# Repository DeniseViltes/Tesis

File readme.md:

# Plataforma experimental de ecualización activa de celdas de litio

Trabajo Profesional de Ingeniería Electrónica  
Facultad de Ingeniería – Universidad de Buenos Aires (FIUBA)  
Año 2026

**Integrantes**
- Sebastián Ezequiel García
- Denise Oriana Viltes

**Tutora:** Dra. Cecilia G. Galarza  
**Cotutor:** Ing. Juan Zuloaga

---

## Descripción

Este proyecto presenta el diseño, simulación e implementación de una plataforma
experimental para evaluar estrategias de ecualización activa en baterías de litio.

La plataforma permite:
- reconfigurar dinámicamente el conexionado de celdas mediante una matriz de switches
<!-- Esto es un comentario --> - estimar SoC (State of Charge)
<!-- Esto es un comentario -->- ensayar algoritmos de balanceo activo
- validar resultados mediante simulación y prototipo físico

El objetivo es contar con una plataforma para comparar
distintas arquitecturas de balanceo y analizar su eficiencia energética.

---

## Estructura del repositorio

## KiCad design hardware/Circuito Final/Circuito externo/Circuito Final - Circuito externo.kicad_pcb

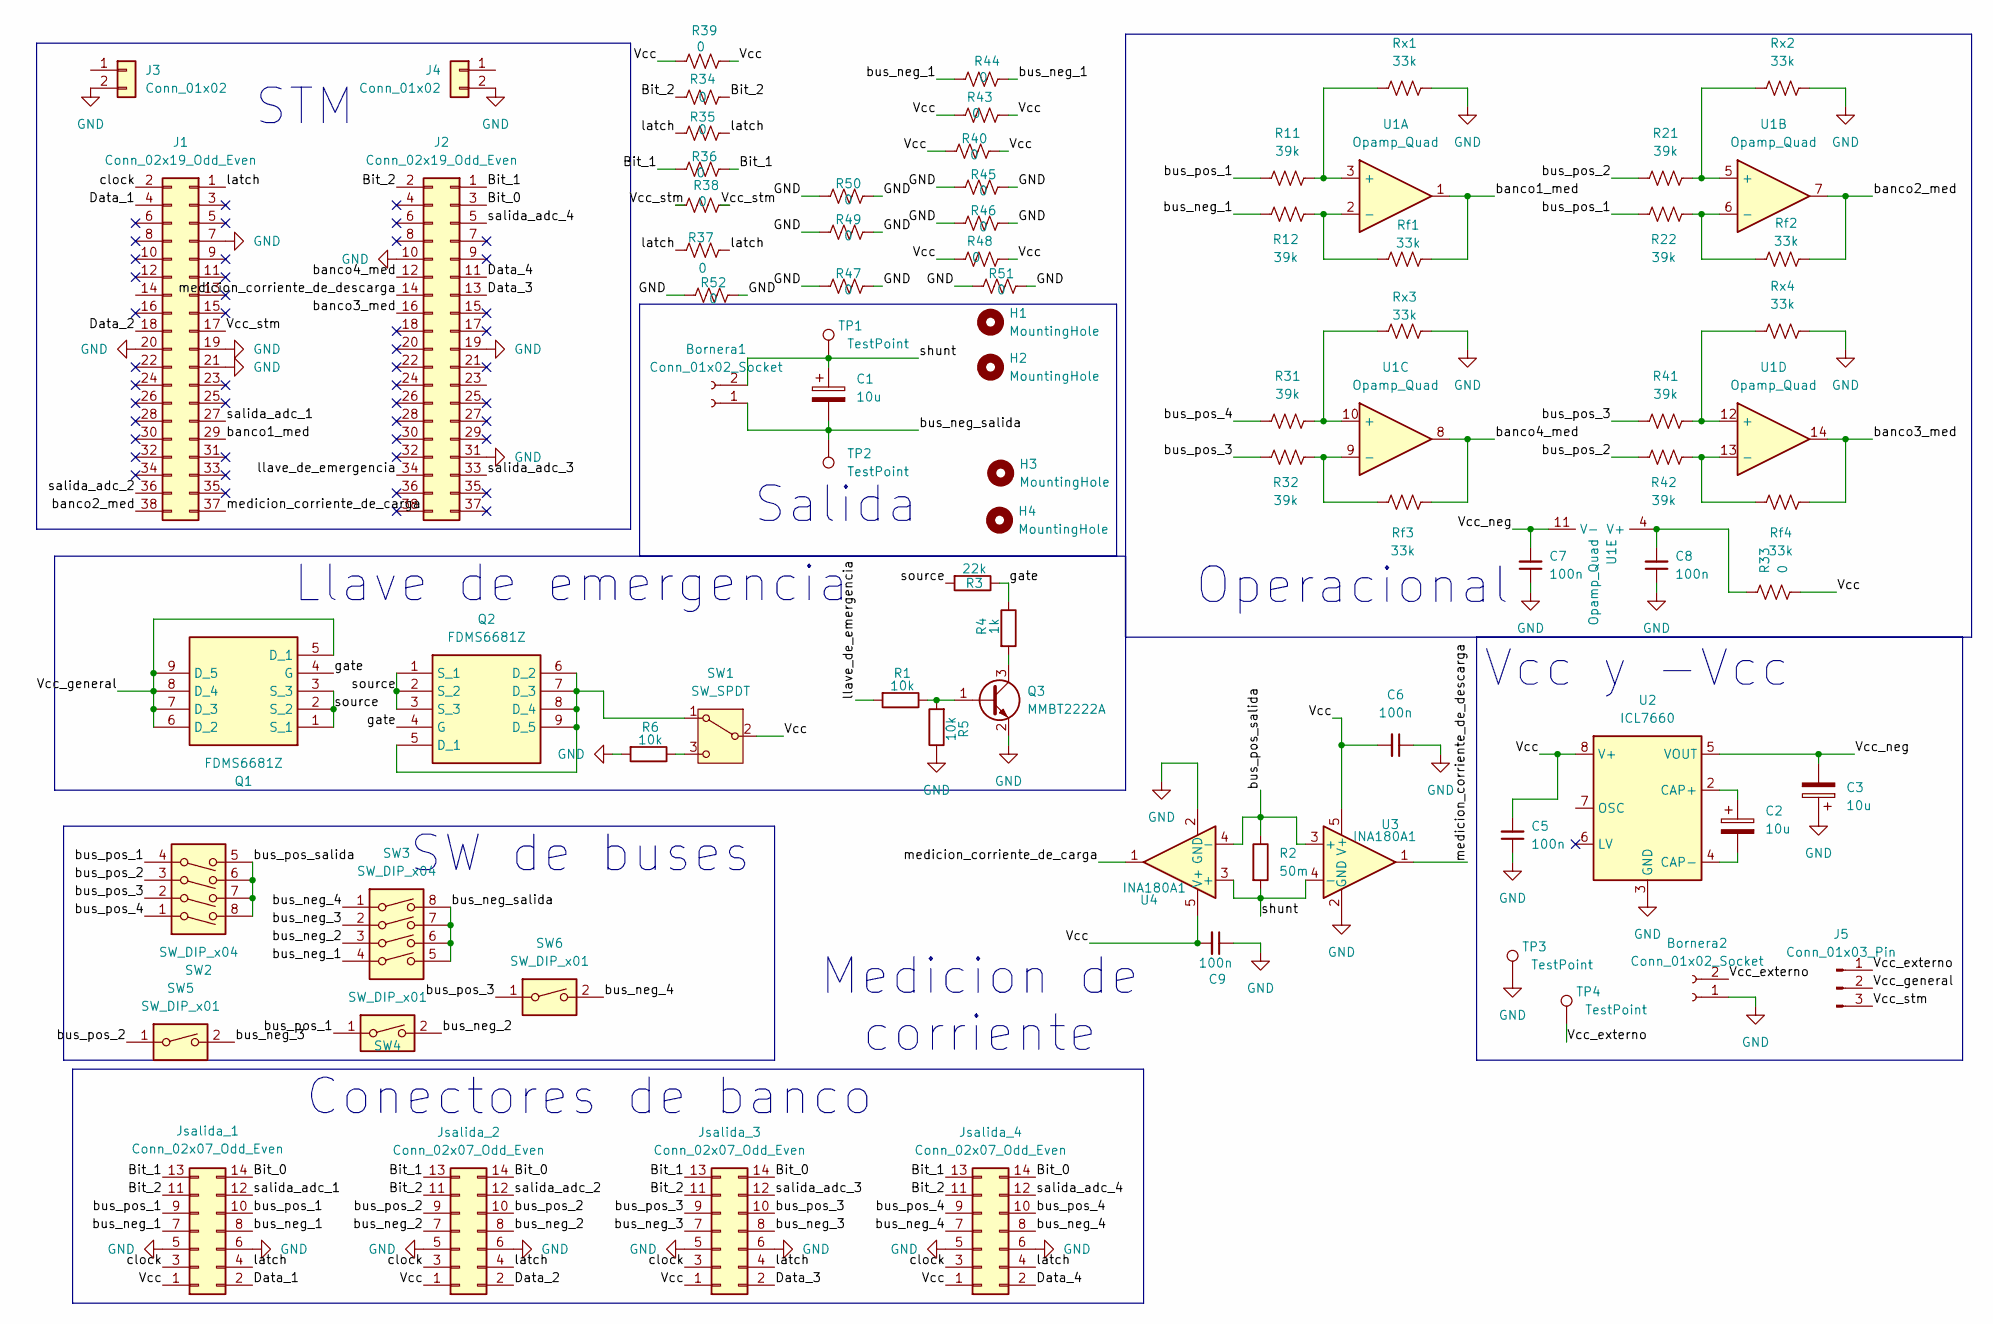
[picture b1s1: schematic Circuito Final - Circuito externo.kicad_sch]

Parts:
Bornera1, Bornera2: Conn_01x02_Socket; TerminalBlock_bornier-2_P5.08mm
C1, C2, C3: 10u; C_1206_3216Metric_Pad1.33x1.80mm_HandSolder
C5, C6, C7, C8, C9: 100n; C_1206_3216Metric_Pad1.33x1.80mm_HandSolder
H1, H2, H3, H4: MountingHole; MountingHole_3.5mm
J1, J2: Conn_02x19_Odd_Even; PinSocket_2x19_P2.54mm_Vertical
J3, J4: Conn_01x02; PinSocket_1x02_P2.54mm_Vertical
J5: Conn_01x03_Pin; PinHeader_1x03_P2.54mm_Vertical
Jsalida_1, Jsalida_2, Jsalida_3, Jsalida_4: Conn_02x07_Odd_Even; IDC-Header_2x07_P2.54mm_Horizontal
Q1, Q2: FDMS6681Z; Mouser Part Number 512-FDMS6681Z
Q3: MMBT2222A; SOT-23
R1, R5, R6: 10k; R_1206_3216Metric_Pad1.30x1.75mm_HandSolder
R2: 50m; R_2512_6332Metric_Pad1.40x3.35mm_HandSolder
R3: 22k; R_1206_3216Metric_Pad1.30x1.75mm_HandSolder
R4: 1k; R_1206_3216Metric_Pad1.30x1.75mm_HandSolder
R11, R12, R21, R22, R31, R32, R41, R42: 39k; R_1206_3216Metric_Pad1.30x1.75mm_HandSolder
R33, R34, R35, R36, R37, R38, R39, R40, R43, R44, R45, R46, R47, R48, R49, R50, R51, R52: 0; R_1206_3216Metric_Pad1.30x1.75mm_HandSolder
Rf1, Rf2, Rf3, Rf4: 33k; R_1206_3216Metric_Pad1.30x1.75mm_HandSolder
Rx1, Rx2, Rx3, Rx4: 33k; R_1206_3216Metric_Pad1.30x1.75mm_HandSolder
SW1: SW_SPDT; SW_Slide_SPDT_Straight_CK_OS102011MS2Q
SW2, SW3: SW_DIP_x04; SW_DIP_SPSTx04_Slide_6.7x11.72mm_W7.62mm_P2.54mm_LowProfile
SW4, SW5, SW6: SW_DIP_x01; SW_DIP_SPSTx01_Slide_9.78x4.72mm_W7.62mm_P2.54mm
TP1, TP2: TestPoint; PinHeader_1x01_P2.54mm_Vertical
TP3, TP4: TestPoint; TestPoint_Keystone_5005-5009_Compact
U1: Opamp_Quad; SO-14_3.9x8.65mm_P1.27mm
U2: ICL7660; SOIC-8_3.9x4.9mm_P1.27mm
U3, U4: INA180A1; SOT-23-5

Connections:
/Bit_0: J2.3, Jsalida_1.14, Jsalida_2.14, Jsalida_3.14, Jsalida_4.14
/Bit_1: J2.1, Jsalida_1.13, Jsalida_2.13, Jsalida_3.13, Jsalida_4.13, R36.1, R36.2
/Bit_2: J2.2, Jsalida_1.11, Jsalida_2.11, Jsalida_3.11, Jsalida_4.11, R34.1, R34.2
/Data_1: J1.4, Jsalida_1.2
/Data_2: J1.18, Jsalida_2.2
/Data_3: J2.13, Jsalida_3.2
/Data_4: J2.11, Jsalida_4.2
/Vcc_externo: Bornera2.2, J5.1, TP4.1 (1_1)
/Vcc_neg: C3.2, C7.2, U1.11 (V-), U2.5 (VOUT)
/Vcc_stm: J1.17, J5.3, R38.1, R38.2
/banco1_med: J1.29, Rf1.2, U1.1
/banco2_med: J1.38, Rf2.2, U1.7
/banco3_med: J2.16, Rf4.2, U1.14
/banco4_med: J2.12, Rf3.2, U1.8
/bus_neg_1: Jsalida_1.7, Jsalida_1.8, R12.2, R44.1, R44.2, SW3.4
/bus_neg_2: Jsalida_2.7, Jsalida_2.8, SW3.3, SW4.2
/bus_neg_3: Jsalida_3.7, Jsalida_3.8, SW3.2, SW5.2
/bus_neg_4: Jsalida_4.7, Jsalida_4.8, SW3.1, SW6.2
/bus_neg_salida: Bornera1.1, C1.2, SW3.5, SW3.6, SW3.7, SW3.8, TP2.1 (1_1)
/bus_pos_1: Jsalida_1.9, Jsalida_1.10, R11.1, R22.2, SW2.4, SW4.1
/bus_pos_2: Jsalida_2.9, Jsalida_2.10, R21.1, R42.2, SW2.3, SW5.1
/bus_pos_3: Jsalida_3.9, Jsalida_3.10, R32.2, R41.1, SW2.2, SW6.1
/bus_pos_4: Jsalida_4.9, Jsalida_4.10, R31.1, SW2.1
/bus_pos_salida: R2.1, SW2.5, SW2.6, SW2.7, SW2.8, U3.3 (+), U4.4 (-)
/clock: J1.2, Jsalida_1.3, Jsalida_2.3, Jsalida_3.3, Jsalida_4.3
/gate: Q1.4 (G), Q2.4 (G), R3.1, R4.1
/latch: J1.1, Jsalida_1.4, Jsalida_2.4, Jsalida_3.4, Jsalida_4.4, R35.1, R35.2, R37.1, R37.2
/llave_de_emergencia: J2.34, R1.2
/medicion_corriente_de_carga: J1.37, U4.1
/medicion_corriente_de_descarga: J2.14, U3.1
/salida_adc_1: J1.27, Jsalida_1.12
/salida_adc_2: J1.36, Jsalida_2.12
/salida_adc_3: J2.33, Jsalida_3.12
/salida_adc_4: J2.5, Jsalida_4.12
/shunt: Bornera1.2, C1.1, R2.2, TP1.1 (1_1), U3.4 (-), U4.3 (+)
/source: Q1.1 (S_1), Q1.2 (S_2), Q1.3 (S_3), Q2.1 (S_1), Q2.2 (S_2), Q2.3 (S_3), R3.2
GND: Bornera2.1, C3.1, C5.1, C6.1, C7.1, C8.1, C9.1, J1.7, J1.19, J1.20, J1.21, J2.10, J2.19, J2.31, J3.2 (Pin_2_2), J4.2 (Pin_2_2), Jsalida_1.5, Jsalida_1.6, Jsalida_2.5, Jsalida_2.6, Jsalida_3.5, Jsalida_3.6, Jsalida_4.5, Jsalida_4.6, Q3.2 (E), R5.1, R6.2, R45.1, R45.2, R46.1, R46.2, R47.1, R47.2, R49.1, R49.2, R50.1, R50.2, R51.1, R51.2, R52.1, R52.2, Rx1.2, Rx2.2, Rx3.2, Rx4.2, TP3.1 (1_1), U2.3 (GND), U3.2 (GND), U4.2 (GND)
unnamed: Q2.5 (D_1), Q2.6 (D_2), Q2.7 (D_3), Q2.8 (D_4), Q2.9 (D_5), SW1.1 (A)
unnamed: Q3.1 (B), R1.1, R5.2
unnamed: Q3.3 (C), R4.2
unnamed: R6.1, SW1.3 (C)
unnamed: R11.2, Rx1.1, U1.3 (+)
unnamed: R12.1, Rf1.1, U1.2 (-)
unnamed: R21.2, Rx2.1, U1.5 (+)
unnamed: R22.1, Rf2.1, U1.6 (-)
unnamed: R31.2, Rx3.1, U1.10 (+)
unnamed: R32.1, Rf3.1, U1.9 (-)
unnamed: R41.2, Rx4.1, U1.12 (+)
unnamed: R42.1, Rf4.1, U1.13 (-)
unnamed: C8.2, R33.2, U1.4 (V+)
unnamed: C2.1, U2.2 (CAP+)
unnamed: C2.2, U2.4 (CAP-)

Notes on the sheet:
Conectores de banco
Llave de emergencia
Salida
STM
SW de buses
Medicion de corriente
Operacional
Vcc y -Vcc

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
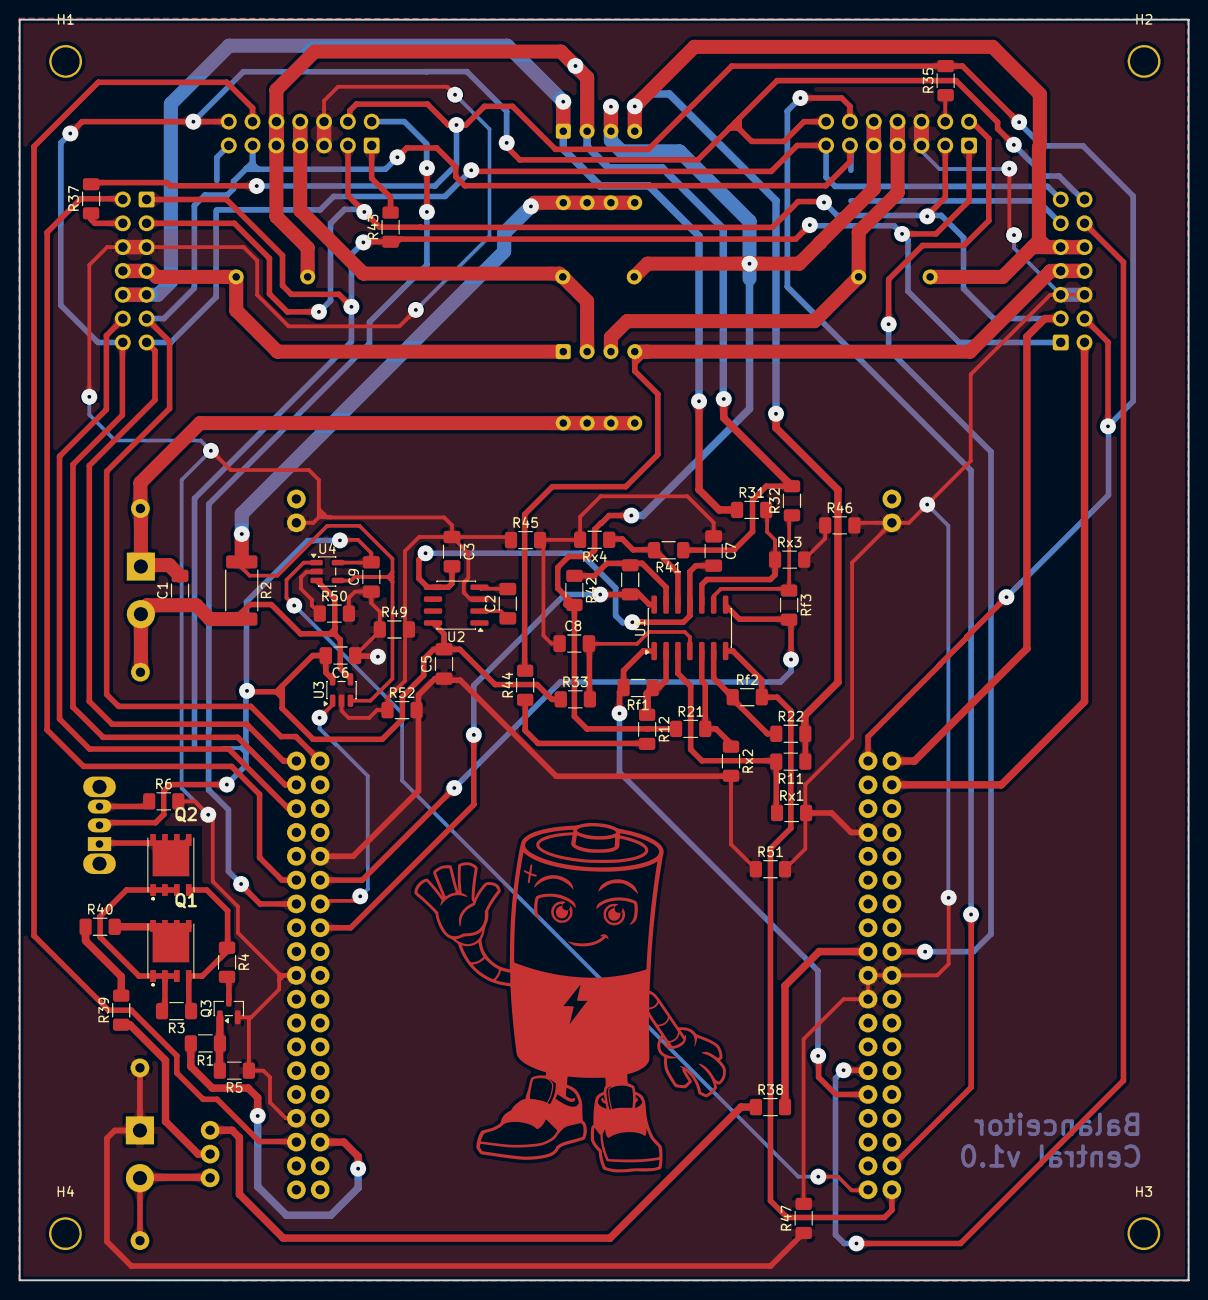
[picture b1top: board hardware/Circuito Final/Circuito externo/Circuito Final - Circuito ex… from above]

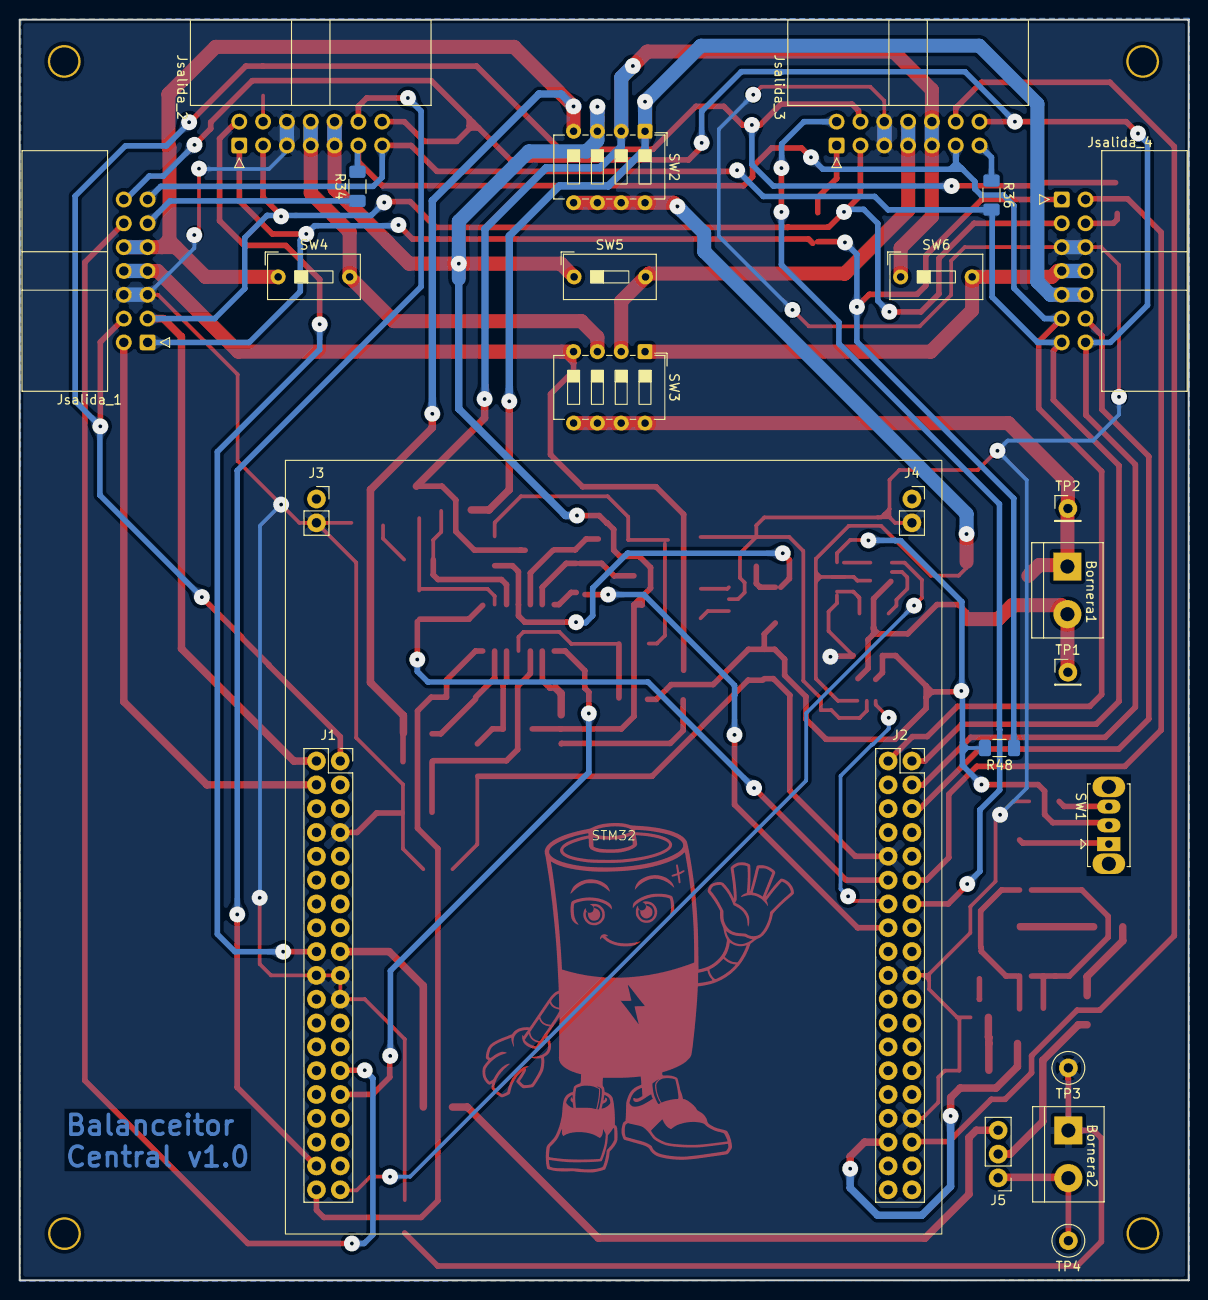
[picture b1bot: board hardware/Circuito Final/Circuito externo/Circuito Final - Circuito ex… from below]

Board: 2 copper layers, 124.6 x 134.4 mm, 81 parts (25 on the bottom side), 54 nets.

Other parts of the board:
STM32: STM32

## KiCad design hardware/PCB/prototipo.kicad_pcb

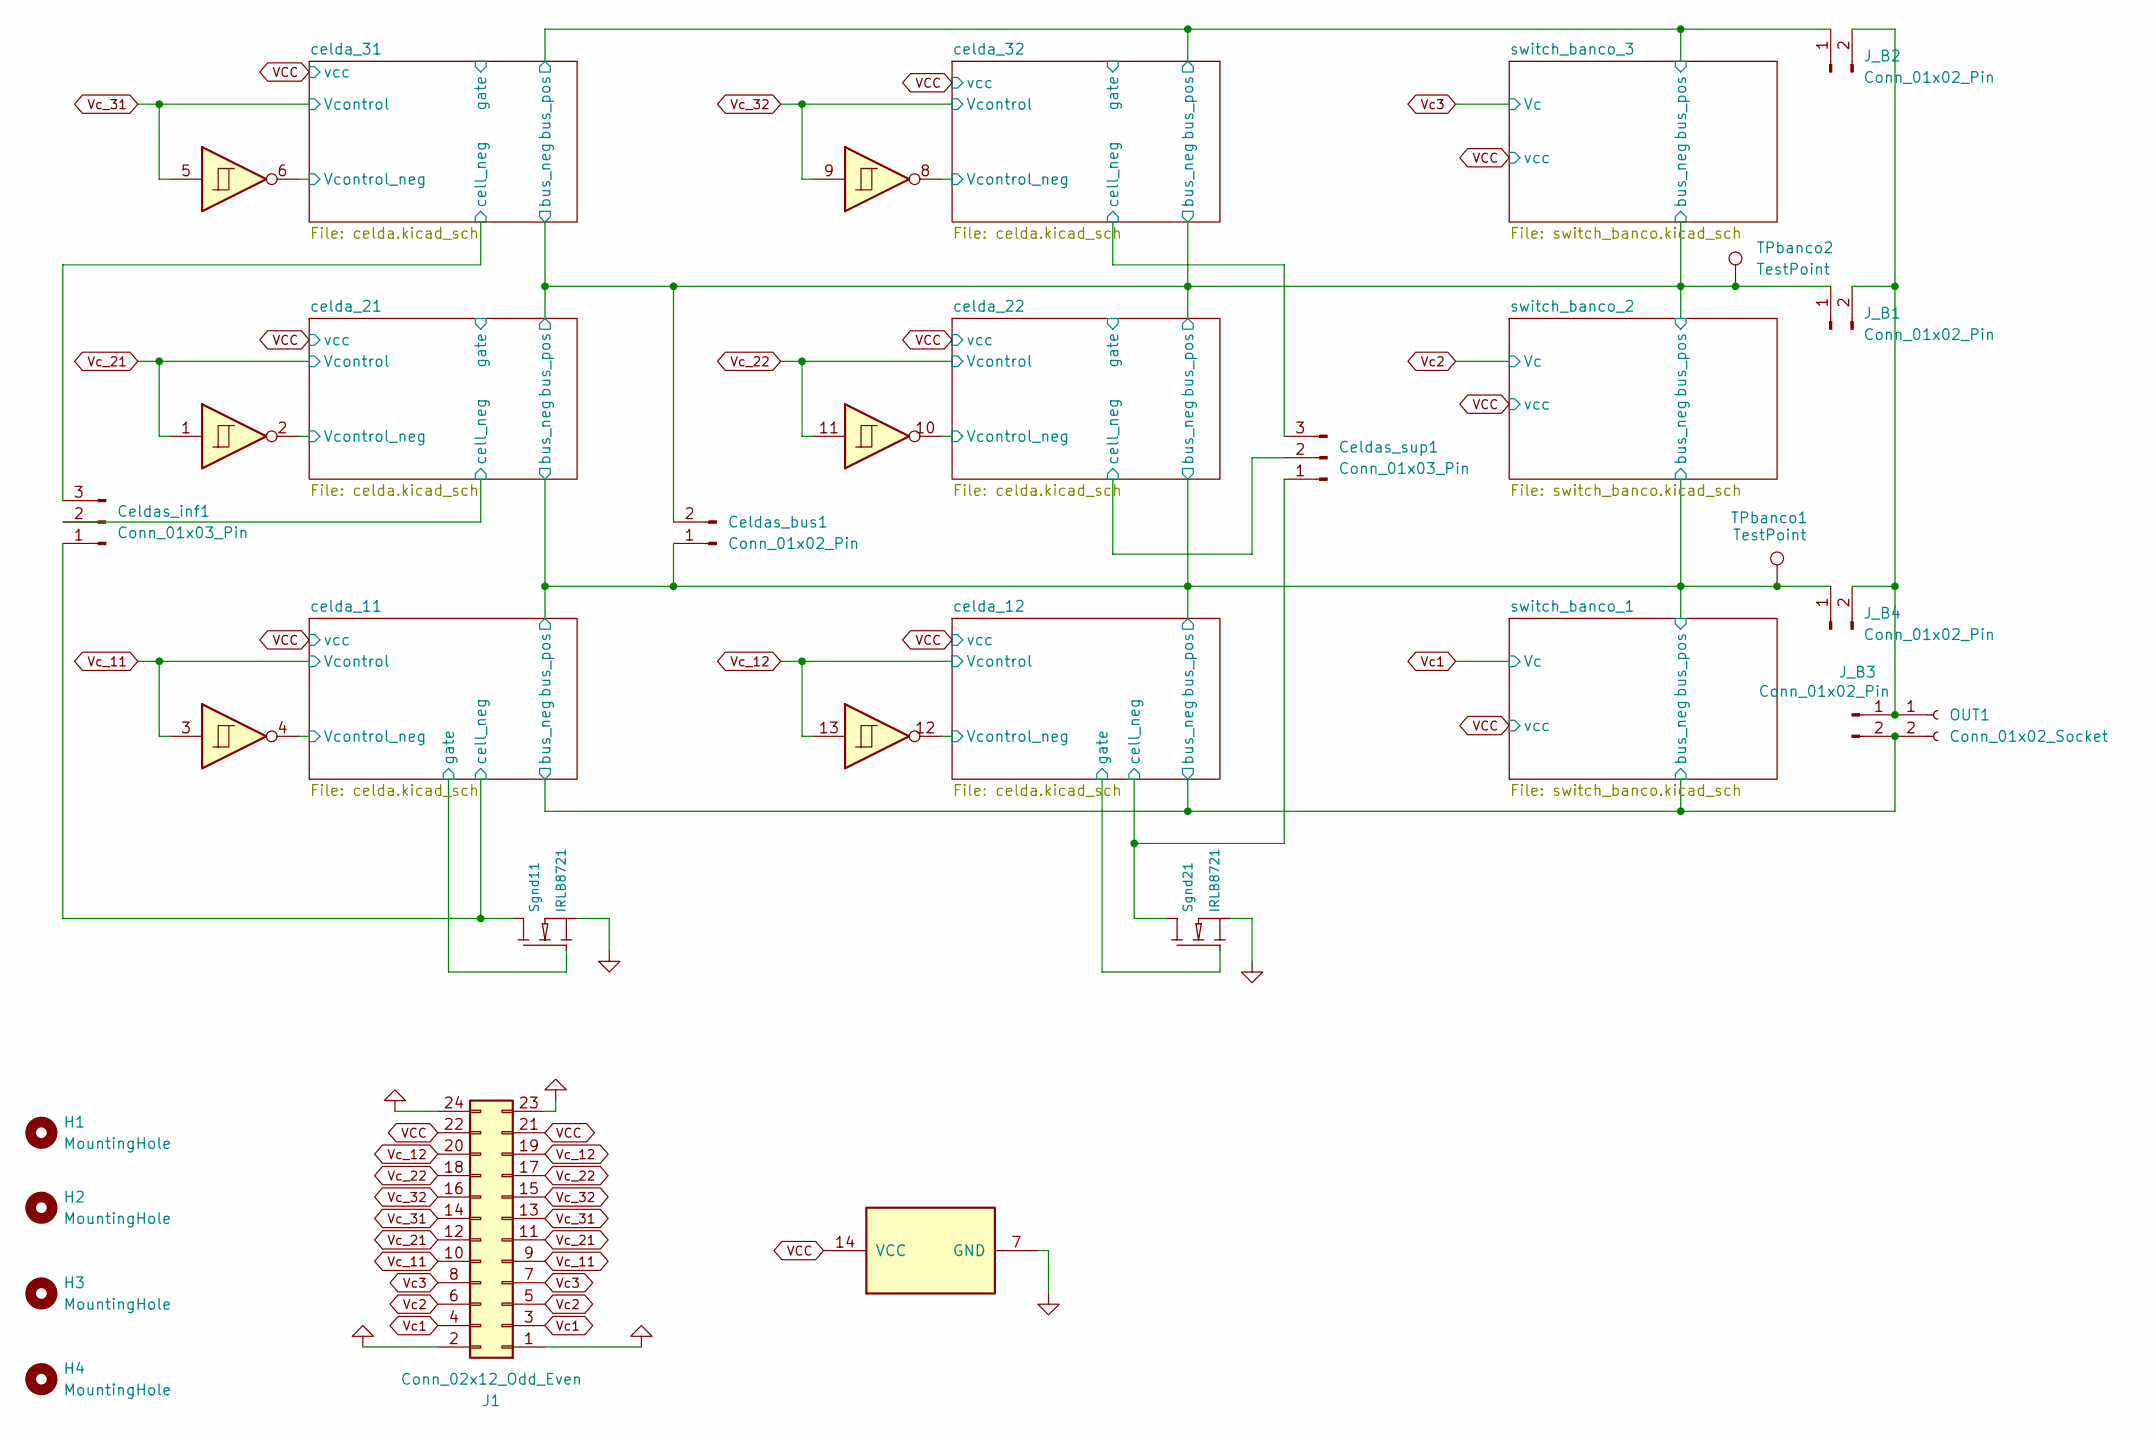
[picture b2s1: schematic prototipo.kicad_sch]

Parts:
A1: DIP-14_W7.62mm_LongPads
Celdas_bus1: Conn_01x02_Pin; PinHeader_1x02_P2.54mm_Vertical
Celdas_inf1: Conn_01x03_Pin; PinHeader_1x03_P2.54mm_Vertical
Celdas_sup1: Conn_01x03_Pin; PinHeader_1x03_P2.54mm_Vertical
H1, H2, H3, H4: MountingHole; MountingHole_3.2mm_M3
J1: Conn_02x12_Odd_Even; PinHeader_2x12_P2.54mm_Vertical
J_B1, J_B2, J_B3, J_B4: Conn_01x02_Pin; PinHeader_1x02_P2.54mm_Vertical
OUT1: Conn_01x02_Socket; TerminalBlock_bornier-2_P5.08mm
Sgnd11, Sgnd21: IRLB8721; TO-220-3_Vertical
TPbanco1, TPbanco2: TestPoint; TestPoint_Bridge_Pitch2.54mm_Drill1.0mm

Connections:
0: A1.7 (GND), J1.1, J1.2, J1.23, J1.24, Sgnd11.3 (S), Sgnd21.3 (S); also elsewhere on the board
/celda_11/Vcontrol_neg: A1.4; also elsewhere on the board
/celda_11/bus_neg: J_B3.2, OUT1.2; also elsewhere on the board
/celda_11/bus_pos: Celdas_bus1.1, J_B4.1, TPbanco1.1 (1_1); also elsewhere on the board
/celda_11/cell_neg: Celdas_inf1.1, Sgnd11.2 (D); also elsewhere on the board
/celda_11/gate: Sgnd11.1 (G); also elsewhere on the board
/celda_12/Vcontrol_neg: A1.12; also elsewhere on the board
/celda_12/cell_neg: Celdas_sup1.1, Sgnd21.2 (D); also elsewhere on the board
/celda_12/gate: Sgnd21.1 (G); also elsewhere on the board
/celda_21/Vcontrol_neg: A1.2; also elsewhere on the board
/celda_21/bus_pos: Celdas_bus1.2, J_B1.1, TPbanco2.1 (1_1); also elsewhere on the board
/celda_21/cell_neg: Celdas_inf1.2; also elsewhere on the board
/celda_22/Vcontrol_neg: A1.10; also elsewhere on the board
/celda_22/cell_neg: Celdas_sup1.2; also elsewhere on the board
/celda_31/Vcontrol_neg: A1.6; also elsewhere on the board
/celda_31/bus_pos: J_B2.1; also elsewhere on the board
/celda_31/cell_neg: Celdas_inf1.3; also elsewhere on the board
/celda_32/Vcontrol_neg: A1.8; also elsewhere on the board
/celda_32/cell_neg: Celdas_sup1.3; also elsewhere on the board
unnamed: J_B1.2, J_B2.2, J_B3.1, J_B4.2, OUT1.1
VCC: A1.14 (VCC), J1.21, J1.22; also elsewhere on the board
Vc1: J1.3, J1.4; also elsewhere on the board
Vc2: J1.5, J1.6; also elsewhere on the board
Vc3: J1.7, J1.8; also elsewhere on the board
Vc_11: A1.3, J1.9, J1.10; also elsewhere on the board
Vc_12: A1.13, J1.19, J1.20; also elsewhere on the board
Vc_21: A1.1, J1.11, J1.12; also elsewhere on the board
Vc_22: A1.11, J1.17, J1.18; also elsewhere on the board
Vc_31: A1.5, J1.13, J1.14; also elsewhere on the board
Vc_32: A1.9, J1.15, J1.16; also elsewhere on the board

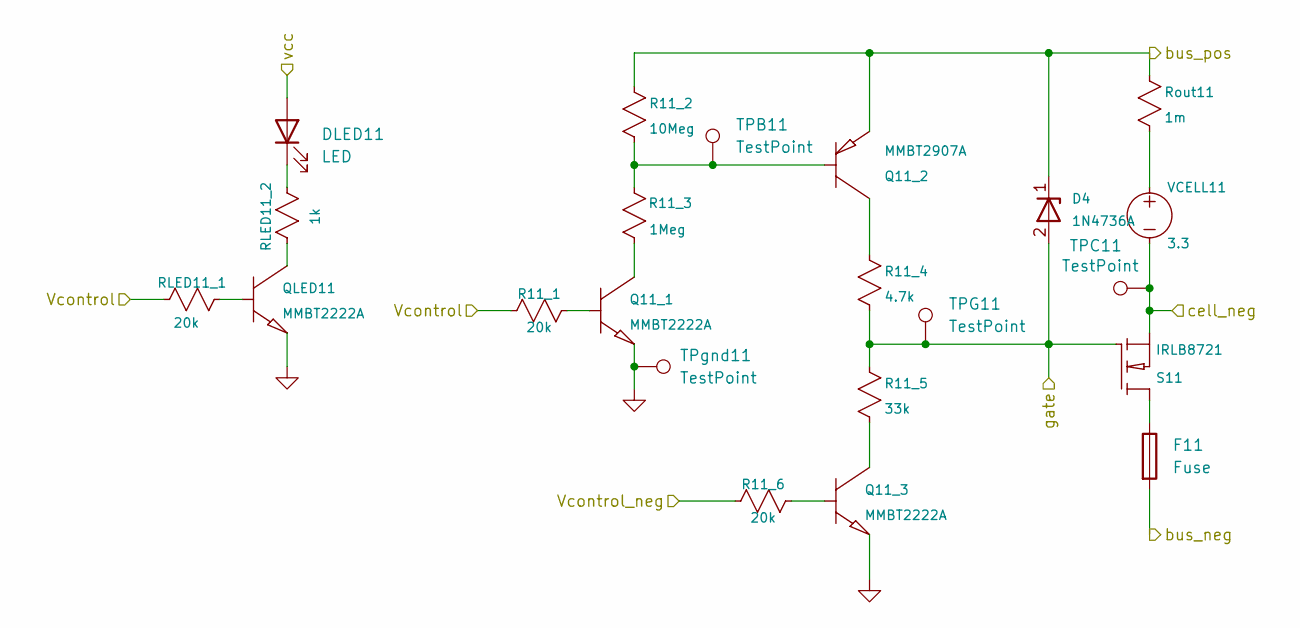
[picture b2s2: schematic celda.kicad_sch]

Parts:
D4: 1N4736A; D_DO-41_SOD81_P7.62mm_Horizontal
DLED11: LED; LED_D5.0mm
F11: Fuse; Fuseholder_Cylinder-5x20mm_Schurter_0031_8201_Horizontal_Op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
Q11_1, Q11_3: MMBT2222A; SOT-23-3
Q11_2: MMBT2907A; SOT-23-3
QLED11: MMBT2222A; SOT-23-3
R11_1, R11_6: 20k; R_Axial_DIN0207_L6.3mm_D2.5mm_P7.62mm_Horizontal
R11_2: 10Meg; R_Axial_DIN0207_L6.3mm_D2.5mm_P7.62mm_Horizontal
R11_3: 1Meg; R_Axial_DIN0207_L6.3mm_D2.5mm_P7.62mm_Horizontal
R11_4: 4.7k; R_Axial_DIN0207_L6.3mm_D2.5mm_P7.62mm_Horizontal
R11_5: 33k; R_Axial_DIN0207_L6.3mm_D2.5mm_P7.62mm_Horizontal
RLED11_1: 20k; R_Axial_DIN0207_L6.3mm_D2.5mm_P7.62mm_Horizontal
RLED11_2: 1k; R_Axial_DIN0207_L6.3mm_D2.5mm_P7.62mm_Horizontal
Rout11: 1m; R_Axial_DIN0207_L6.3mm_D2.5mm_P7.62mm_Horizontal
S11: IRLB8721; TO-220-3_Vertical
TPB11: TestPoint; TestPoint_Bridge_Pitch2.54mm_Drill1.0mm
TPC11: TestPoint; TestPoint_Bridge_Pitch2.54mm_Drill1.0mm
TPG11: TestPoint; TestPoint_Bridge_Pitch2.54mm_Drill1.0mm
TPgnd11: TestPoint; TestPoint_Bridge_Pitch2.54mm_Drill1.0mm
VCELL11: 3.3; BatteryHolder_MPD_BK-18650-PC2

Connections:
0: Q11_1.2 (E), Q11_3.2 (E), QLED11.2 (E), TPgnd11.1 (1_1); also elsewhere on the board
/celda_11/Vcontrol_neg: R11_6.2; also elsewhere on the board
/celda_11/bus_neg: F11.2; also elsewhere on the board
/celda_11/bus_pos: D4.1 (K), Q11_2.2 (E), R11_2.1, Rout11.1; also elsewhere on the board
/celda_11/cell_neg: S11.3 (S), TPC11.1 (1_1), VCELL11.2 (-); also elsewhere on the board
/celda_11/gate: D4.2 (A), R11_4.2, R11_5.1, S11.1 (G), TPG11.1 (1_1); also elsewhere on the board
unnamed: DLED11.1 (K), RLED11_2.1
unnamed: Q11_1.1 (B), R11_1.1
unnamed: Q11_1.3 (C), R11_3.2
unnamed: Q11_2.1 (B), R11_2.2, R11_3.1, TPB11.1 (1_1)
unnamed: Q11_2.3 (C), R11_4.1
unnamed: Q11_3.1 (B), R11_6.1
unnamed: Q11_3.3 (C), R11_5.2
unnamed: QLED11.1 (B), RLED11_1.1
unnamed: QLED11.3 (C), RLED11_2.2
unnamed: F11.1, S11.2 (D)
unnamed: Rout11.2, VCELL11.1 (+)
VCC: DLED11.2 (A); also elsewhere on the board
Vc_11: R11_1.2, RLED11_1.2; also elsewhere on the board

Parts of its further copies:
D5, D6, D7, D8, D9: 1N4736A; D_DO-41_SOD81_P7.62mm_Horizontal
DLED12, DLED21, DLED22, DLED31, DLED32: LED; LED_D5.0mm
F12, F21, F22, F31, F32: Fuse; Fuseholder_Cylinder-5x20mm_Schurter_0031_8201_Horizontal_Op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
Q12_1, Q12_3, Q21_1, Q21_3, Q22_1, Q22_3, Q31_1, Q31_3, Q32_1, Q32_3: MMBT2222A; SOT-23-3
Q12_2, Q21_2, Q22_2, Q31_2, Q32_2: MMBT2907A; SOT-23-3
QLED21, QLED22, QLED31, QLED32: MMBT2222A; SOT-23-3
QLED_12: MMBT2222A; SOT-23-3
R12_1, R12_6, R21_1, R21_6, R22_1, R22_6, R31_1, R31_6, R32_1, R32_6: 20k; R_Axial_DIN0207_L6.3mm_D2.5mm_P7.62mm_Horizontal
R12_2, R21_2, R22_2, R31_2, R32_2: 10Meg; R_Axial_DIN0207_L6.3mm_D2.5mm_P7.62mm_Horizontal
R12_3, R21_3, R22_3, R31_3, R32_3: 1Meg; R_Axial_DIN0207_L6.3mm_D2.5mm_P7.62mm_Horizontal
R12_4, R21_4, R22_4, R31_4, R32_4: 4.7k; R_Axial_DIN0207_L6.3mm_D2.5mm_P7.62mm_Horizontal
R12_5, R21_5, R22_5, R31_5, R32_5: 33k; R_Axial_DIN0207_L6.3mm_D2.5mm_P7.62mm_Horizontal
RLED12_1, RLED21_1, RLED22_1, RLED31_1, RLED32_1: 20k; R_Axial_DIN0207_L6.3mm_D2.5mm_P7.62mm_Horizontal
RLED12_2, RLED21_2, RLED22_2, RLED31_2, RLED32_2: 1k; R_Axial_DIN0207_L6.3mm_D2.5mm_P7.62mm_Horizontal
Rout12, Rout21, Rout22, Rout31, Rout32: 1m; R_Axial_DIN0207_L6.3mm_D2.5mm_P7.62mm_Horizontal
S12, S21, S22, S31, S32: IRLB8721; TO-220-3_Vertical
TPB12, TPB21, TPB22, TPB31, TPB32: TestPoint; TestPoint_Bridge_Pitch2.54mm_Drill1.0mm
TPC12, TPC21, TPC22, TPC31, TPC32: TestPoint; TestPoint_Bridge_Pitch2.54mm_Drill1.0mm
TPG12, TPG21, TPG22, TPG31, TPG32: TestPoint; TestPoint_Bridge_Pitch2.54mm_Drill1.0mm
TPgnd12, TPgnd21, TPgnd22, TPgnd31, TPgnd32: TestPoint; TestPoint_Bridge_Pitch2.54mm_Drill1.0mm
VCELL12, VCELL21, VCELL22, VCELL31, VCELL32: 3.3; BatteryHolder_MPD_BK-18650-PC2

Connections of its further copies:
0: Q12_1.2 (E), Q12_3.2 (E), Q21_1.2 (E), Q21_3.2 (E), Q22_1.2 (E), Q22_3.2 (E), Q31_1.2 (E), Q31_3.2 (E), Q32_1.2 (E), Q32_3.2 (E), QLED21.2 (E), QLED22.2 (E), QLED31.2 (E), QLED32.2 (E), QLED_12.2 (E), TPgnd12.1 (1_1), TPgnd21.1 (1_1), TPgnd22.1 (1_1), TPgnd31.1 (1_1), TPgnd32.1 (1_1); also elsewhere on the board
/celda_11/bus_neg: F12.2; also elsewhere on the board
/celda_11/bus_pos: D6.1 (K), F21.2, F22.2, Q12_2.2 (E), R12_2.1, Rout12.1; also elsewhere on the board
/celda_12/Vcontrol_neg: R12_6.2; also elsewhere on the board
/celda_12/cell_neg: S12.3 (S), TPC12.1 (1_1), VCELL12.2 (-); also elsewhere on the board
/celda_12/gate: D6.2 (A), R12_4.2, R12_5.1, S12.1 (G), TPG12.1 (1_1); also elsewhere on the board
/celda_21/Vcontrol_neg: R21_6.2; also elsewhere on the board
/celda_21/bus_pos: D5.1 (K), D7.1 (K), F31.2, F32.2, Q21_2.2 (E), Q22_2.2 (E), R21_2.1, R22_2.1, Rout21.1, Rout22.1; also elsewhere on the board
/celda_21/cell_neg: S21.3 (S), TPC21.1 (1_1), VCELL21.2 (-); also elsewhere on the board
/celda_21/gate: D5.2 (A), R21_4.2, R21_5.1, S21.1 (G), TPG21.1 (1_1)
/celda_22/Vcontrol_neg: R22_6.2; also elsewhere on the board
/celda_22/cell_neg: S22.3 (S), TPC22.1 (1_1), VCELL22.2 (-); also elsewhere on the board
/celda_22/gate: D7.2 (A), R22_4.2, R22_5.1, S22.1 (G), TPG22.1 (1_1)
/celda_31/Vcontrol_neg: R31_6.2; also elsewhere on the board
/celda_31/bus_pos: D8.1 (K), D9.1 (K), Q31_2.2 (E), Q32_2.2 (E), R31_2.1, R32_2.1, Rout31.1, Rout32.1; also elsewhere on the board
/celda_31/cell_neg: S31.3 (S), TPC31.1 (1_1), VCELL31.2 (-); also elsewhere on the board
/celda_31/gate: D8.2 (A), R31_4.2, R31_5.1, S31.1 (G), TPG31.1 (1_1)
/celda_32/Vcontrol_neg: R32_6.2; also elsewhere on the board
/celda_32/cell_neg: S32.3 (S), TPC32.1 (1_1), VCELL32.2 (-); also elsewhere on the board
/celda_32/gate: D9.2 (A), R32_4.2, R32_5.1, S32.1 (G), TPG32.1 (1_1)
unnamed: DLED12.1 (K), RLED12_2.1
unnamed: DLED21.1 (K), RLED21_2.1
unnamed: DLED22.1 (K), RLED22_2.1
unnamed: DLED31.1 (K), RLED31_2.1
unnamed: DLED32.1 (K), RLED32_2.1
unnamed: Q12_1.1 (B), R12_1.1
unnamed: Q12_1.3 (C), R12_3.2
unnamed: Q12_2.1 (B), R12_2.2, R12_3.1, TPB12.1 (1_1)
unnamed: Q12_2.3 (C), R12_4.1
unnamed: Q12_3.1 (B), R12_6.1
unnamed: Q12_3.3 (C), R12_5.2
unnamed: Q21_1.1 (B), R21_1.1
unnamed: Q21_1.3 (C), R21_3.2
unnamed: Q21_2.1 (B), R21_2.2, R21_3.1, TPB21.1 (1_1)
unnamed: Q21_2.3 (C), R21_4.1
unnamed: Q21_3.1 (B), R21_6.1
unnamed: Q21_3.3 (C), R21_5.2
unnamed: Q22_1.1 (B), R22_1.1
unnamed: Q22_1.3 (C), R22_3.2
unnamed: Q22_2.1 (B), R22_2.2, R22_3.1, TPB22.1 (1_1)
unnamed: Q22_2.3 (C), R22_4.1
unnamed: Q22_3.1 (B), R22_6.1
unnamed: Q22_3.3 (C), R22_5.2
unnamed: Q31_1.1 (B), R31_1.1
unnamed: Q31_1.3 (C), R31_3.2
unnamed: Q31_2.1 (B), R31_2.2, R31_3.1, TPB31.1 (1_1)
unnamed: Q31_2.3 (C), R31_4.1
unnamed: Q31_3.1 (B), R31_6.1
unnamed: Q31_3.3 (C), R31_5.2
unnamed: Q32_1.1 (B), R32_1.1
unnamed: Q32_1.3 (C), R32_3.2
unnamed: Q32_2.1 (B), R32_2.2, R32_3.1, TPB32.1 (1_1)
unnamed: Q32_2.3 (C), R32_4.1
unnamed: Q32_3.1 (B), R32_6.1
unnamed: Q32_3.3 (C), R32_5.2
unnamed: QLED21.1 (B), RLED21_1.1
unnamed: QLED21.3 (C), RLED21_2.2
unnamed: QLED22.1 (B), RLED22_1.1
unnamed: QLED22.3 (C), RLED22_2.2
unnamed: QLED31.1 (B), RLED31_1.1
unnamed: QLED31.3 (C), RLED31_2.2
unnamed: QLED32.1 (B), RLED32_1.1
unnamed: QLED32.3 (C), RLED32_2.2
unnamed: QLED_12.1 (B), RLED12_1.1
unnamed: QLED_12.3 (C), RLED12_2.2
unnamed: F12.1, S12.2 (D)
unnamed: F21.1, S21.2 (D)
unnamed: F22.1, S22.2 (D)
unnamed: F31.1, S31.2 (D)
unnamed: F32.1, S32.2 (D)
unnamed: Rout12.2, VCELL12.1 (+)
unnamed: Rout21.2, VCELL21.1 (+)
unnamed: Rout22.2, VCELL22.1 (+)
unnamed: Rout31.2, VCELL31.1 (+)
unnamed: Rout32.2, VCELL32.1 (+)
VCC: DLED12.2 (A), DLED21.2 (A), DLED22.2 (A), DLED31.2 (A), DLED32.2 (A); also elsewhere on the board
Vc_12: R12_1.2, RLED12_1.2; also elsewhere on the board
Vc_21: R21_1.2, RLED21_1.2; also elsewhere on the board
Vc_22: R22_1.2, RLED22_1.2; also elsewhere on the board
Vc_31: R31_1.2, RLED31_1.2; also elsewhere on the board
Vc_32: R32_1.2, RLED32_1.2; also elsewhere on the board

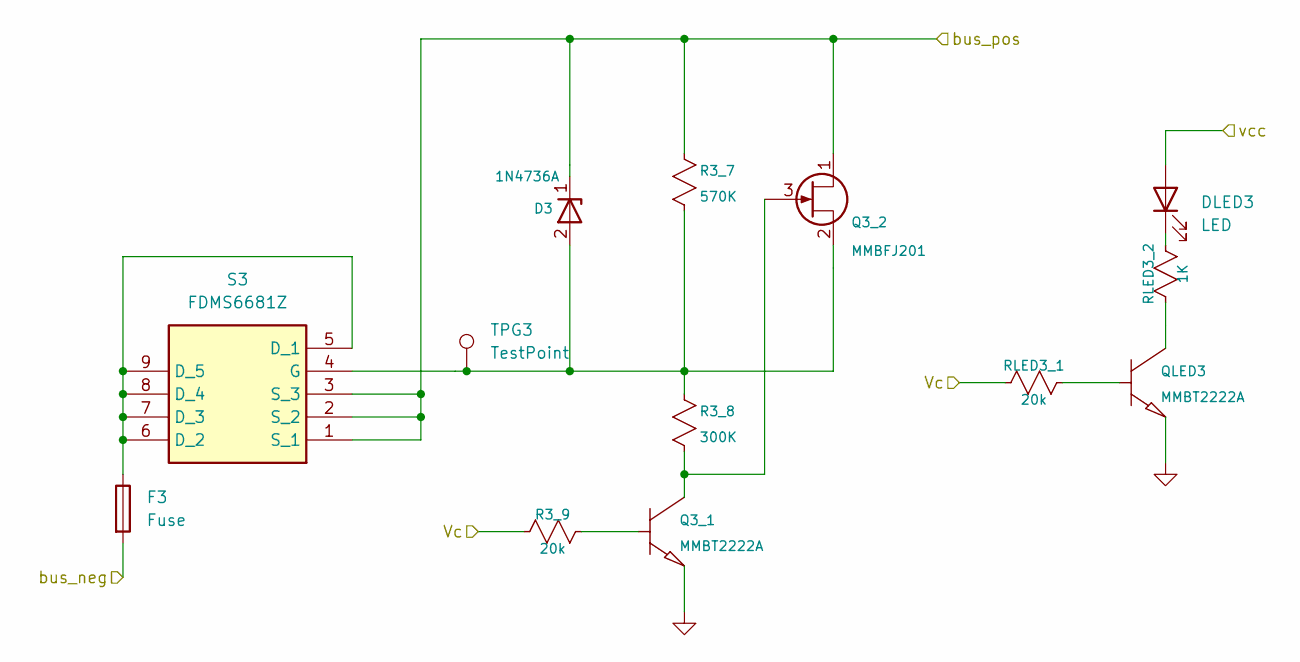
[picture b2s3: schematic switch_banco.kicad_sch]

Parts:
D3: 1N4736A; D_DO-41_SOD81_P7.62mm_Horizontal
DLED3: LED; LED_D5.0mm
F3: Fuse; Fuseholder_Cylinder-5x20mm_Schurter_0031_8201_Horizontal_Op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
Q3_1: MMBT2222A; SOT-23-3
Q3_2: MMBFJ201; SOT-23-3
QLED3: MMBT2222A; SOT-23-3
R3_7: 570K; R_Axial_DIN0207_L6.3mm_D2.5mm_P7.62mm_Horizontal
R3_8: 300K; R_Axial_DIN0207_L6.3mm_D2.5mm_P7.62mm_Horizontal
R3_9: 20k; R_Axial_DIN0207_L6.3mm_D2.5mm_P7.62mm_Horizontal
RLED3_1: 20k; R_Axial_DIN0207_L6.3mm_D2.5mm_P7.62mm_Horizontal
RLED3_2: 1K; R_Axial_DIN0207_L6.3mm_D2.5mm_P7.62mm_Horizontal
S3: FDMS6681Z; Mouser Part Number 512-FDMS6681Z
TPG3: TestPoint; TestPoint_Bridge_Pitch2.54mm_Drill1.0mm

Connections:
0: Q3_1.2 (E), QLED3.2 (E); also elsewhere on the board
/celda_21/bus_pos: F3.2; also elsewhere on the board
/celda_31/bus_pos: D3.1 (K), Q3_2.1 (D), R3_7.1, S3.1 (S_1), S3.2 (S_2), S3.3 (S_3); also elsewhere on the board
unnamed: D3.2 (A), Q3_2.2 (S), R3_7.2, R3_8.1, S3.4 (G), TPG3.1 (1_1)
unnamed: DLED3.1 (K), RLED3_2.1
unnamed: Q3_1.1 (B), R3_9.1
unnamed: Q3_1.3 (C), Q3_2.3 (G), R3_8.2
unnamed: QLED3.1 (B), RLED3_1.1
unnamed: QLED3.3 (C), RLED3_2.2
unnamed: F3.1, S3.5 (D_1), S3.6 (D_2), S3.7 (D_3), S3.8 (D_4), S3.9 (D_5)
VCC: DLED3.2 (A); also elsewhere on the board
Vc3: R3_9.2, RLED3_1.2; also elsewhere on the board

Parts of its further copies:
D1, D2: 1N4736A; D_DO-41_SOD81_P7.62mm_Horizontal
DLED1, DLED2: LED; LED_D5.0mm
F1, F2: Fuse; Fuseholder_Cylinder-5x20mm_Schurter_0031_8201_Horizontal_Op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
Q1_1, Q2_1: MMBT2222A; SOT-23-3
Q1_2, Q2_2: MMBFJ201; SOT-23-3
QLED1, QLED2: MMBT2222A; SOT-23-3
R1_7, R2_7: 570K; R_Axial_DIN0207_L6.3mm_D2.5mm_P7.62mm_Horizontal
R1_8, R2_8: 300K; R_Axial_DIN0207_L6.3mm_D2.5mm_P7.62mm_Horizontal
R1_9, R2_9: 20k; R_Axial_DIN0207_L6.3mm_D2.5mm_P7.62mm_Horizontal
RLED1_1, RLED2_1: 20k; R_Axial_DIN0207_L6.3mm_D2.5mm_P7.62mm_Horizontal
RLED1_2, RLED2_2: 1K; R_Axial_DIN0207_L6.3mm_D2.5mm_P7.62mm_Horizontal
S1, S2: FDMS6681Z; Mouser Part Number 512-FDMS6681Z
TPG1, TPG2: TestPoint; TestPoint_Bridge_Pitch2.54mm_Drill1.0mm

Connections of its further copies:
0: Q1_1.2 (E), Q2_1.2 (E), QLED1.2 (E), QLED2.2 (E); also elsewhere on the board
/celda_11/bus_neg: F1.2; also elsewhere on the board
/celda_11/bus_pos: D1.1 (K), F2.2, Q1_2.1 (D), R1_7.1, S1.1 (S_1), S1.2 (S_2), S1.3 (S_3); also elsewhere on the board
/celda_21/bus_pos: D2.1 (K), Q2_2.1 (D), R2_7.1, S2.1 (S_1), S2.2 (S_2), S2.3 (S_3); also elsewhere on the board
unnamed: D1.2 (A), Q1_2.2 (S), R1_7.2, R1_8.1, S1.4 (G), TPG1.1 (1_1)
unnamed: D2.2 (A), Q2_2.2 (S), R2_7.2, R2_8.1, S2.4 (G), TPG2.1 (1_1)
unnamed: DLED1.1 (K), RLED1_2.1
unnamed: DLED2.1 (K), RLED2_2.1
unnamed: Q1_1.1 (B), R1_9.1
unnamed: Q1_1.3 (C), Q1_2.3 (G), R1_8.2
unnamed: Q2_1.1 (B), R2_9.1
unnamed: Q2_1.3 (C), Q2_2.3 (G), R2_8.2
unnamed: QLED1.1 (B), RLED1_1.1
unnamed: QLED1.3 (C), RLED1_2.2
unnamed: QLED2.1 (B), RLED2_1.1
unnamed: QLED2.3 (C), RLED2_2.2
unnamed: F1.1, S1.5 (D_1), S1.6 (D_2), S1.7 (D_3), S1.8 (D_4), S1.9 (D_5)
unnamed: F2.1, S2.5 (D_1), S2.6 (D_2), S2.7 (D_3), S2.8 (D_4), S2.9 (D_5)
VCC: DLED1.2 (A), DLED2.2 (A); also elsewhere on the board
Vc1: R1_9.2, RLED1_1.2; also elsewhere on the board
Vc2: R2_9.2, RLED2_1.2; also elsewhere on the board
